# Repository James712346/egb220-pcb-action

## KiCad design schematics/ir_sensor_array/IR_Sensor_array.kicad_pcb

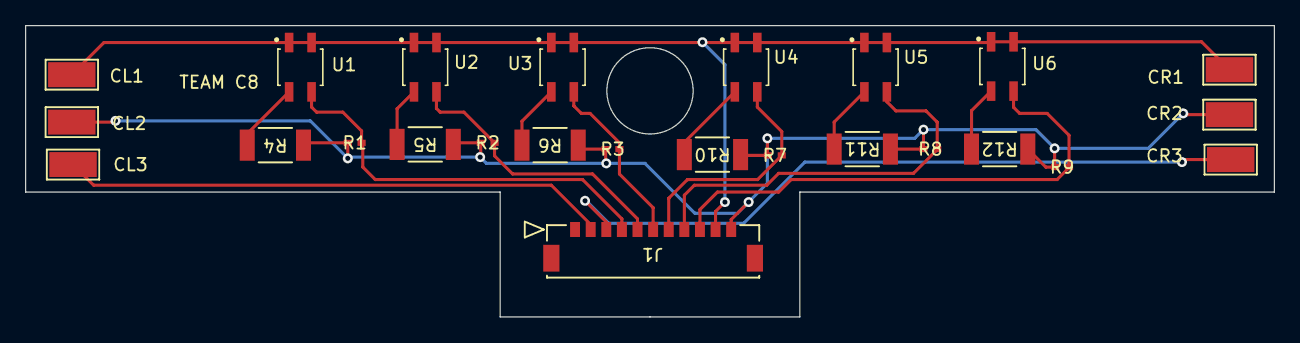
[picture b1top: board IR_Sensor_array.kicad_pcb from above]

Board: 2 copper layers, 100.0 x 23.3 mm, 25 parts (0 on the bottom side), 16 nets.

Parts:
CL1, CL2, CL3: TestPoint_Keystone_5019_Minature
CR1, CR2, CR3: TestPoint_Keystone_5019_Minature
J1: 5055671171; CON_5055671171
R1, R2, R3, R7, R8, R9: ERJ-2RKF4702X(47k); RC0402N_PAN
R4, R5, R6, R10, R11, R12: ERJ-12ZYJ470U(47); RC2010N_PAN
U1, U2, U3, U4, U5, U6: QRE1113GR; SOIC180P460X187-4N

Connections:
GND: CL1.1, CR1.1, J1.10 (VOUT2), U1.1, U1.4, U2.1, U2.4, U3.1, U3.4, U4.1, U4.4, U5.1, U5.4, U6.1, U6.4
unnamed: R4.2, U1.2
unnamed: R5.2, U2.2
unnamed: R6.2, U3.2
unnamed: R10.2, U4.2
unnamed: R11.2, U5.2
unnamed: R12.2, U6.2
VCC: CL2.1, CR2.1, J1.11 (VOUT1), R1.1, R2.1, R3.1, R4.1, R5.1, R6.1, R7.1, R8.1, R9.1, R10.1, R11.1, R12.1
VOUT1: J1.4 (VOUT8), R1.2, U1.3
VOUT2: J1.5 (VOUT7), R2.2, U2.3
VOUT3: J1.6 (VOUT6), R3.2, U3.3
VOUT4: J1.7 (VOUT5), R7.2, U4.3
VOUT5: J1.8 (VOUT4), R8.2, U5.3
VOUT6: J1.9 (VOUT3), R9.2, U6.3
VOUT7: CR3.1, J1.3 (VOUT9)
VOUT8: CL3.1, J1.2 (VOUT10)

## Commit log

2024-04-18 Cating the package.txt
2024-04-18 Output text file
2024-04-18 Settings Tess dpi
2024-04-18 Trying a higher dpi
2024-04-18 setting dpi to limit
2024-04-18 Try 1000 dpi
2024-04-18 Copol
2024-04-18 Try this with set oem and psm
2024-04-18 oem 0
2024-04-23 Trying new git action
2024-04-23 forgot test cases
2024-04-23 Jq to list folders
2024-04-23 set output
2024-04-23 updated setting of values, and added captuire all
2024-04-23 setting up files correctly
2024-04-23 Focusing on librepcb atm
2024-04-23 Forgot to build them
2024-04-23 removing /tmp/
2024-04-23 newer version of librePCB
2024-04-23 Fixed version
2024-04-23 curious
2024-04-23 removed sudo
2024-04-23 debugging listing of gerber
2024-04-24 Forgot to change output step id
2024-04-24 maybe quotation
2024-04-24 forgot $
2024-04-24 Attempt at downloading all artifacts
2024-04-24 forgot to include file in the env
2024-04-25 Print all profiles
2024-04-25 sudo needed
2024-04-25 Fixed Empty strag
2024-04-25 debugging time :)
2024-04-25 Lets try echo print statments
2024-04-25 adding Pricing
2024-04-25 adding png lib
2024-04-25 try 2
2024-04-25 its the god dam image variable aaahhhh
2024-04-25 Added more indepth Sizing and calculations
2024-04-25 seperate the file names
2024-04-25 adding json component
2024-04-25 removed ID
2024-04-25 adding image pushing and processing
2024-04-25 attempt to fix json
2024-04-25 change key format
2024-04-25 forgot to push this too :0
2024-04-25 Echo lists
2024-04-25 Fixed list if statment
2024-04-25 attempting to get kicad execption passes
2024-04-25 Trying to get that if statment to call now
2024-04-25 workout why
2024-04-25 checkout is broken atm, lets first see if i can not ru kicad
2024-04-25 on to github checkout error yay
2024-04-25 too good, fixed on the first commit
2024-04-25 add keys to images
2024-04-25 see if my custom one works
2024-04-25 try new release
2024-04-25 Remove old actions
2024-04-25 its not getting the latest release
2024-04-25 yolo
2024-04-25 trying the old way
2024-04-25 added release job
2024-04-25 removed whitespace between eqeual on line one of generate readme
2024-04-25 Echo out all the json files
2024-04-25 Fixed Jq error, and few other items
2024-04-25 fixed up a few errors
2024-04-25 Zip up gerber files, and added json string
2024-04-25 Spelt gerber wrong
2024-04-25 trying to get jq to return the correct values
2024-04-25 escape the pricing
2024-04-25 echo silkscreen urls
2024-04-25 added tables
2024-04-25 stripped the image variable
2024-04-25 time to look at extracted text
2024-04-25 Fixing extract text
2024-04-25 Adding EOF to file
2024-04-25 new line might help
2024-04-25 try getting rid of \n in extracted text
2024-04-26 just printing extracted text
2024-04-26 Needed to escape the code ticks, as they are handled like quotes
2024-04-26 No longer need to remove /r and /n
2024-04-26 Adding bottom silk layer
2024-04-26 trying to add a new job
2024-04-26 Format Project
2024-04-26 try this
2024-04-26 get board on it own
2024-04-26 Adding EGB220 Checks
2024-04-26 Get Board works
2024-04-26 attempt 1, setting to string
2024-04-26 trying to get it to loop
2024-04-26 forgot to stage echo
2024-04-26 I feel so stupid
2024-04-26 this should work
2024-04-26 attempt 2
2024-04-26 debugging time
2024-04-26 This should fix the board looping issue
2024-04-26 add better team check, and added None flag
2024-04-26 remove exit
2024-04-26 adding some echos
2024-04-26 seperatating code
2024-04-26 grep causing a exit 1, so perl will be used instead
2024-04-26 Final Fixes
2024-04-26 Adding Global env
2024-04-26 Better Packaging Logic
2024-04-26 change of axis
2024-04-26 Fixed up a few packaging issues and added echo of project and boardname
2024-04-26 Fixed naming issue in package (Hopefully)
2024-04-27 attempting kicad
2024-04-27 New PCB
2024-04-27 xhwxk if it exists
2024-04-27 Try cd into project file
2024-04-27 realised kibot is inside a docker container
2024-04-27 using $(pwd) instead of .
2024-04-27 silly forgot about cat cmd
2024-04-27 changed to .
2024-04-27 fix up config
2024-04-27 setting up artifact
2024-04-27 setting dir
2024-04-27 try again without .
2024-04-27 added * to try and remove archieve tree
2024-04-27 archieving myself
2024-04-27 cd instead
2024-04-27 mv it outside working dir
2024-04-27 sudo that bitch
2024-04-27 YOLO complete directory
2024-04-27 Removed the rm .
2024-04-27 Update pcb.yml
    New tree
2024-04-27 Update pcb.yml
    I not sure why, but let's see
2024-04-28 try this to package -NPTH file with boardname
2024-04-28 add .drl to the exclude line for boardname
2024-04-28 lowering the case of all file names
2024-05-14 added outputs
